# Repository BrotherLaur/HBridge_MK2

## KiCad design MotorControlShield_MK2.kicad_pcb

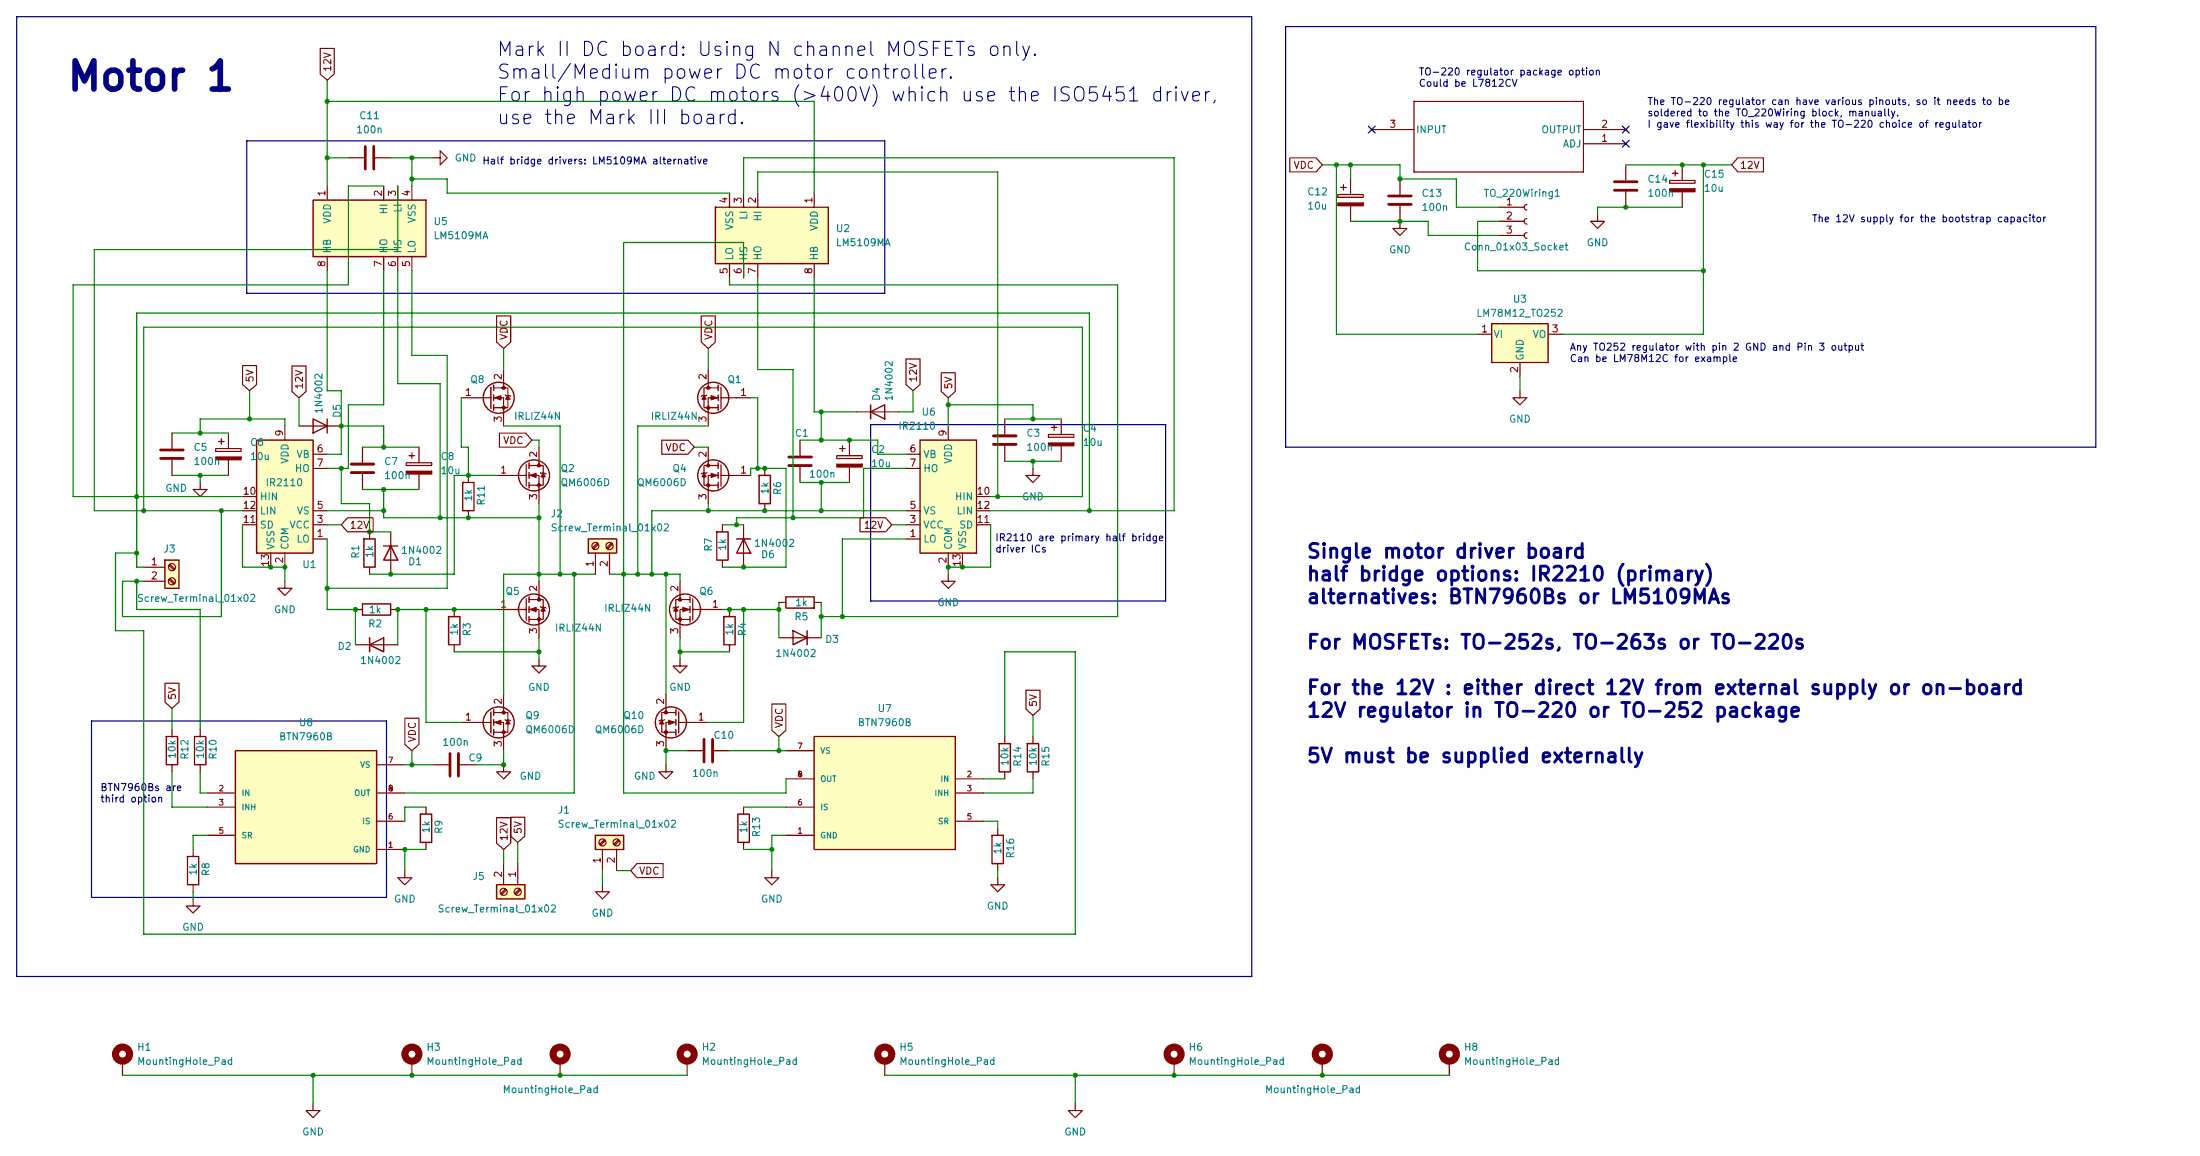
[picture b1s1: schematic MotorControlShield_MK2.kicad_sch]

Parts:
AMS11173V3: LM317T; TO-220-3_Horizontal_TabDown
C1, C3, C5, C7, C9, C10, C11, C13, C14: 100n; C_Rect_L7.0mm_W3.5mm_P5.00mm
C2, C4, C6, C8, C12, C15: 10u; CP_Elec_6.3x3.9_COMPOSITE
D1, D2, D3, D4, D5, D6: 1N4002; D_DO-41_SOD81_P10.16mm_Horizontal
H1, H2, H3, H4, H5, H6, H7, H8: MountingHole_Pad; MountingHole_2.7mm_M2.5_Pad_Via
J1, J2, J3, J5: Screw_Terminal_01x02; TerminalBlock_CLEAN_2PIN
Q1, Q5, Q6, Q8: IRLIZ44N; TO-220-3_EXTENDED2
Q2, Q4, Q9, Q10: QM6006D; TO-263-2
R1, R2, R3, R4, R5, R6, R7, R8, R9, R11, R13, R16: 1k; R_Axial_Clean
R10, R12, R14, R15: 10k; R_Axial_Clean
TO_220Wiring1: Conn_01x03_Socket; PinHeader_1x03_P2.54mm_Vertical
U1, U6: IR2110; DIP-14_W7.62mm
U2, U5: LM5109MA; SOIC-8_3.9x4.9mm_P1.27mm
U3: LM78M12_TO252; TO-252-2
U7, U8: BTN7960B; IC_BTN7960B; PARTREV 1.0

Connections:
5V: C3.1, C4.1, C5.1, C6.1, J5.1, R12.2, R15.2, U1.9 (VDD), U6.9 (VDD)
12V: C11.1, C14.1, C15.1, D4.2 (A), D5.2 (A), J5.2, TO_220Wiring1.2, U1.3 (VCC), U2.1 (VDD), U3.3 (VO), U5.1 (VDD), U6.3 (VCC)
GND: C3.2, C4.2, C5.2, C6.2, C9.2, C10.2, C11.2, C12.2, C13.2, C14.2, C15.2, H1.1, H2.1, H3.1, H4.1, H5.1, H6.1, H7.1, H8.1, J1.1, Q5.3 (S), Q6.3 (S), Q9.3 (S), Q10.3 (S), R3.1, R4.1, R8.1, R9.1, R13.1, R16.1, TO_220Wiring1.3, U1.2 (COM), U1.11 (SD), U1.13 (VSS), U2.4 (VSS), U3.2 (GND), U5.4 (VSS), U6.2 (COM), U6.11 (SD), U6.13 (VSS), U7.1 (GND), U8.1 (GND)
unnamed: D1.2 (A), Q2.1 (G), Q8.1 (G), R1.1, R11.2
unnamed: D1.1 (K), R1.2, U1.7 (HO), U5.7 (HO)
unnamed: D2.2 (A), Q5.1 (G), Q9.1 (G), R2.1, R3.2
unnamed: D2.1 (K), R2.2, U1.1 (LO), U5.5 (LO)
unnamed: D3.2 (A), Q6.1 (G), Q10.1 (G), R4.2, R5.1
unnamed: D3.1 (K), R5.2, U2.5 (LO), U6.1 (LO)
unnamed: C1.1, C2.1, D4.1 (K), U2.8 (HB), U6.6 (VB)
unnamed: C7.1, C8.1, D5.1 (K), U1.6 (VB), U5.8 (HB)
unnamed: D6.2 (A), Q1.1 (G), Q4.1 (G), R6.2, R7.1
unnamed: D6.1 (K), R7.2, U2.7 (HO), U6.7 (HO)
unnamed: C7.2, C8.2, J2.1, Q2.3 (S), Q5.2 (D), Q8.3 (S), Q9.2 (D), R11.1, U1.5 (VS), U5.6 (HS), U8.4 (OUT), U8.8 (OUT)
unnamed: C1.2, C2.2, J2.2, Q1.3 (S), Q4.3 (S), Q6.2 (D), Q10.2 (D), R6.1, U2.6 (HS), U6.5 (VS), U7.4 (OUT), U7.8 (OUT)
unnamed: J3.1, R14.2, U1.10 (HIN), U2.3 (LI), U5.2 (HI), U6.12 (LIN)
unnamed: J3.2, R10.2, U1.12 (LIN), U2.2 (HI), U5.3 (LI), U6.10 (HIN)
unnamed: R14.1, U7.2 (IN)
unnamed: R15.1, U7.3 (INH)
unnamed: R13.2, U7.6 (IS)
unnamed: R16.2, U7.5 (SR)
unnamed: R10.1, U8.2 (IN)
unnamed: R12.1, U8.3 (INH)
unnamed: R9.2, U8.6 (IS)
unnamed: R8.2, U8.5 (SR)
VDC: C9.1, C10.1, C12.1, C13.1, J1.2, Q1.2 (D), Q2.2 (D), Q4.2 (D), Q8.2 (D), TO_220Wiring1.1, U3.1 (VI), U7.7 (VS), U8.7 (VS)

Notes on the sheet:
BTN7960Bs are third option
Single motor driver board half bridge options: IR2210 (primary) alternatives: BTN7960Bs or LM5109MAs For MOSFETs: TO-252s, TO-263s or TO-220s For the 12V : either direct 12V from external supply or on-board 12V regulator in TO-220 or TO-252 package 5V must be supplied externally
Half bridge drivers: LM5109MA alternative
Any TO252 regulator with pin 2 GND and Pin 3 output Can be LM78M12C for example
The 12V supply for the bootstrap capacitor
TO-220 regulator package option Could be L7812CV
Motor 1
The TO-220 regulator can have various pinouts, so it needs to be soldered to the TO_220Wiring block, manually. I gave flexibility this way for the TO-220 choice of regulator
IR2110 are primary half bridge driver ICs
Mark II DC board: Using N channel MOSFETs only. Small/Medium power DC motor controller. For high power DC motors (>400V) which use the ISO5451 driver, use the Mark III board.

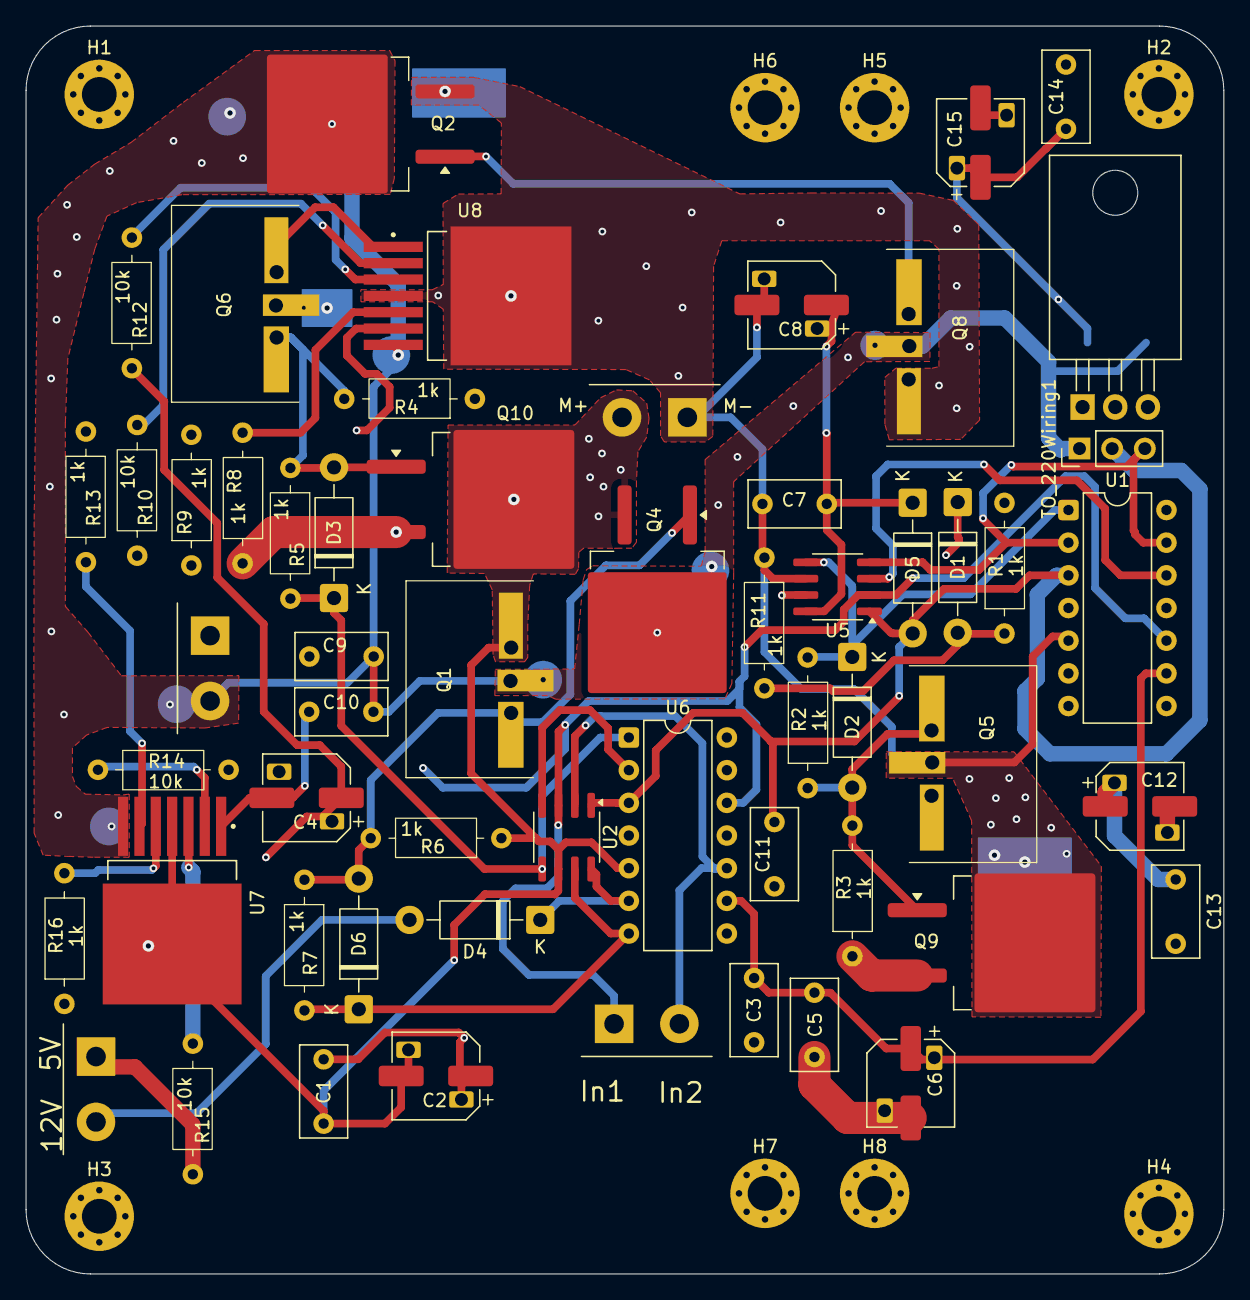
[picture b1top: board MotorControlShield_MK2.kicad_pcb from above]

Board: 4 copper layers, 93.1 x 97.0 mm, 66 parts (1 on the bottom side), 26 nets.

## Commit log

2025-10-07 Added documentation/layout
2025-10-08 Added pads for extra current
2025-10-08 Made self contained footprints
